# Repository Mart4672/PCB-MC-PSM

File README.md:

# PCB-MC-PSM
Modular/Configurable Power Supply Module (PSM) Board. This PCB works as a standalone PSM that also has high current connections for servos and mosfets.

## Modular/Configurable PSM Board "Version-A" Features
- Power Supply Module board that supports power, servos, and mosfets
    - all high current devices should be managed by this board
- Supports a battery input voltage range that covers 6 to 16.8V
    - This voltage range ensures that 2s to 4s LiPo batteries can be used
- Has a PMIC that outputs a regulated 5V and supports at least 5A continuous
- Has a high current diode rectifier to support a second power input
    - intended for a secondary battery or a power supply for keeping the main PSM battery from discharging
- Has terminal blocks for battery connections

TODO
- 5 Mosfet channels
    - 2 5V channels
    - 3 VBatt channels
    - continuity checking on all channels
        - optionally uses alternative continuity circuit (NFET instead of voltage divider) [1/15/2025]
    - current limiting resistors or fuses on all channels
        - uses a high wattage-rated resistor to limit the current to a level that the traces can handle
- 4 Servo connections
    - uses a screwless terminal block connection
        - ex: TE 1-2834015-4 Buchanan WireMate
    - uses inline PTC fuses for each servo
- Connectors for STEVE board signals
    - Uses screwless terminal block connectors or JST-GH connectors
    - Servo PWM signals (4)
    - Mosfet gate signals (5)
    - Mosfet continuity signals (5)
    - Battery Voltage sensing lines (1)

- import/assign missing 3D part models

## Future Updates

### Future PSM Board Updates
- create additional PSM boards with more/less features depending on desired capability
    - ex: a larger PSM board with a second PMIC to support more servos and mosfets
    - ex: a smaller PSM board with fewer supported servos/mosfets and/or a lower current rating
- use a PMOS mosfet for reverse polarity protection
- current draw sensing that can be reported to the main STEVE board

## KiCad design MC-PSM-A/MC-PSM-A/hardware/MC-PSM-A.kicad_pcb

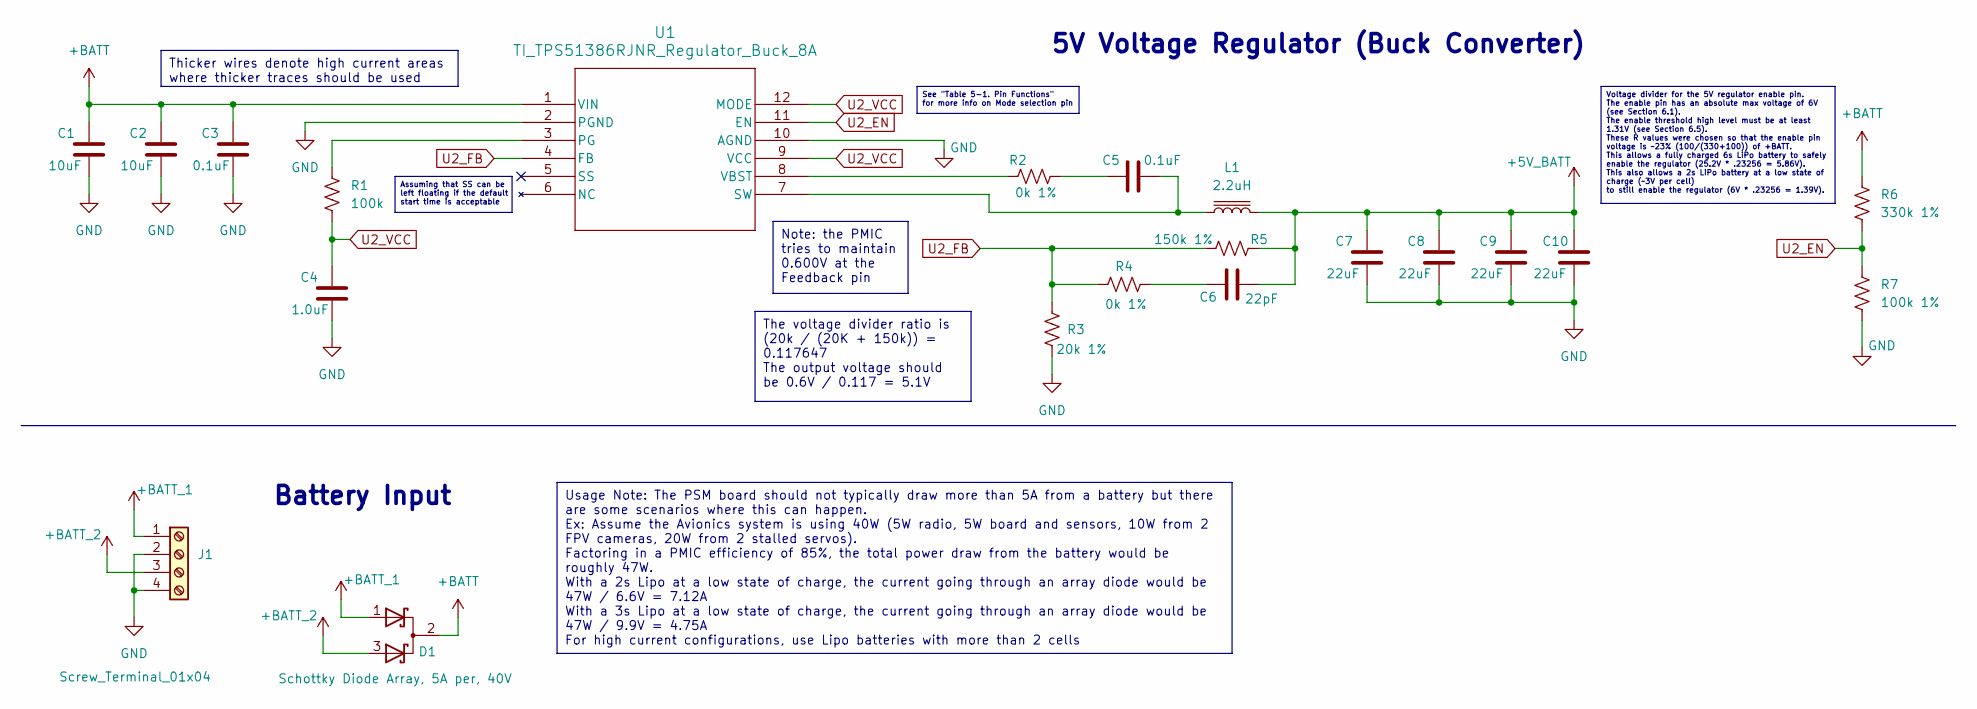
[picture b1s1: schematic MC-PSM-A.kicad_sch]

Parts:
C1, C2: 10uF; C_1206_3216Metric
C3, C5: 0.1uF; C_0603_1608Metric
C4: 1.0uF; C_0603_1608Metric
C6: 22pF; C_0603_1608Metric
C7, C8, C9, C10: 22uF; C_1206_3216Metric
D1: Schottky Diode Array, 5A per, 40V; PDS1040CTL-13_PowerDI-5
J1: Screw_Terminal_01x04; TerminalBlock_Phoenix_PT-1,5-4-5.0-H_1x04_P5.00mm_Horizontal
L1: 2.2uH; L_Coilcraft_XAL6060-XXX
R1: 100k; R_0603_1608Metric
R2, R4: 0k 1%; R_0603_1608Metric
R3: 20k 1%; R_0603_1608Metric
R5: 150k 1%; R_0603_1608Metric
R6: 330k 1%; R_0603_1608Metric
R7: 100k 1%; R_0603_1608Metric
U1: TI_TPS51386RJNR_Regulator_Buck_8A; TI_TPS51386RJNR_VQFN-HR_REG_BUCK_8A

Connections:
+5V_BATT: C6.2, C7.1, C8.1, C9.1, C10.1, L1.2, R5.2
+BATT: C1.1, C2.1, C3.1, D1.2 (K), R6.1, U1.1 (VIN)
+BATT_1: D1.1 (A), J1.1
+BATT_2: D1.3 (A), J1.3
GND: C1.2, C2.2, C3.2, C4.2, C7.2, C8.2, C9.2, C10.2, J1.2, J1.4, R3.1, R7.2, U1.2 (PGND), U1.10 (AGND)
unnamed: C5.1, R2.2
unnamed: C6.1, R4.2
unnamed: R1.1, U1.3 (PG)
unnamed: C5.2, L1.1, U1.7 (SW)
unnamed: R2.1, U1.8 (VBST)
U2_EN: R6.2, R7.1, U1.11 (EN)
U2_FB: R3.2, R4.1, R5.1, U1.4 (FB)
U2_VCC: C4.1, R1.2, U1.9 (VCC), U1.12 (MODE)

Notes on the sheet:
Thicker wires denote high current areas where thicker traces should be used
See "Table 5-1. Pin Functions" for more info on Mode selection pin
Voltage divider for the 5V regulator enable pin. The enable pin has an absolute max voltage of 6V (see Section 6.1). The enable threshold high level must be at least 1.31V (see Section 6.5). These R values were chosen so that the enable pin voltage is ~23% (100/(330+100)) of +BATT. This allows a fu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
The voltage divider ratio is (20k / (20K + 150k)) = 0.117647 The output voltage should be 0.6V / 0.117 = 5.1V
Note: the PMIC tries to maintain 0.600V at the Feedback pin
Assuming that SS can be left floating if the default start time is acceptable
Usage Note: The PSM board should not typically draw more than 5A from a battery but there are some scenarios where this can happen. Ex: Assume the Avionics system is using 40W (5W radio, 5W board and sensors, 10W from 2 FPV cameras, 20W from 2 stalled servos). Factoring in a PMIC efficiency of 85%,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
5V Voltage Regulator (Buck Converter)
Battery Input

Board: 2 copper layers, 19 parts (0 on the bottom side), 9 nets, no tracks yet.

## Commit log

2025-04-20 Created KiCad Project; added PMIC and batt input to schematic
    Created KiCad Project; added PMIC and batt input to schematic. Still need to import the proper footprint for the PMIC. Updated README with features
